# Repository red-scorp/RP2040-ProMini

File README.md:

```
 ______  ______ ______   ______   __     ______     ______           ______  _       _ 
(_____ \(_____ (_____ \ / __   | / /    / __   |   (_____ \         |  ___ \(_)     (_)
 _____) )_____) )____) ) | //| |/ /____| | //| |___ _____) )___ ___ | | _ | |_ ____  _ 
(_____ (|  ____//_____/| |// | |___   _) |// | (___)  ____/ ___) _ \| || || | |  _ \| |
      | | |     _______|  /__| |   | | |  /__| |   | |   | |  | |_| | || || | | | | | |
      |_|_|    (_______)\_____/    |_|  \_____/    |_|   |_|   \___/|_||_||_|_|_| |_|_|
```

# RP2040-ProMini Project

The RP2040-ProMini project aims to create a replacement for the Arduino Pro Mini using the RP2040 MCU.

## RP2040-ProMini Board

The **RP2040-ProMini** board is a 4-layer board designed to accommodate the popular Raspberry Pi RP2040 MCU in the commonly used, but obsolete, Arduino Pro Mini footprint.

Preview:

You can view the [Schematics in PDF format](doc/RP2040-ProMini.pdf) for detailed information.

STEP 3D files are available [with pins](doc/RP2040-ProMini-with-pins.step) and [without pins](doc/RP2040-ProMini-board.step).

Features:

- Arduino Pro Mini compatible pinout
- Partially compatible with Arduino Nano RP2040 Connect pinout
- _(v3.x)_ Detachable USB and JTAG extension board with RESET button
- Dual-core Cortex-M0+ Raspberry Pi RP2040
- Small footprint suitable for DIY projects
- _(v1.x)_ 19 GPIO pins, including 4 analog inputs or _(v2.x-v3.x)_ 21 GPIO pins, including 4 analog inputs
- USB data pins on the side connector
- SWD debugging pins on the side connector
- _(v1.x)_ LDO-based 3.3V power supply with a maximum 16V input or _(v2.x-v3.x)_ Buck-Boost converter based 3.3V power supply with input range of 2.5V-12V
- Supports both SOIC and WSON 16MB flash packages
- Flat back side enables use as a sub-assembly
- Two cut points to reduce power consumption of unused components

CAM files, as well as the BOM and CPL files for JLCPCB, are available.

### Board Pinout

Following pinout is used for the board:

| Board Pin | RP2040 Pin | Function | Notes |
| --------- | ---------- | -------- | ----- |
| D0        | GPIO1      | UART0 TX |       |
| D1        | GPIO0      | UART0 RX |       |
| D2        | GPIO25     |          |       |
| D3        | GPIO15     |          |       |
| D4        | GPIO16     |          |       |
| D5        | GPIO17     |          |       |
| D6        | GPIO18     |          |       |
| D7        | GPIO19     |          |       |
| D8        | GPIO20     |          |       |
| D9        | GPIO21     |          |       |
| D10       | GPIO5      | SS       |       |
| D11       | GPIO7      | MOSI     |       |
| D12       | GPIO4      | MISO     |       |
| D13       | GPIO6      | SCK      | LED   |
| D14 A0    | GPIO26     |          |       |
| D15 A1    | GPIO27     |          |       |
| D16 A2    | GPIO28     |          |       |
| D17 A3    | GPIO29     |          |       |
| D18       | GPIO12     | SDA      |       |
| D19       | GPIO13     | SCL      |       |
| D20       | GPIO22     |          |       |
| D21       | GPIO23     |          |       |

### Cut Points

There are two cut points on the board to reduce power consumption of unused components.

| Cut Point | Function | Notes |
| --------- | -------- | ----- |
| CUT_VIN   | Separates VIN-to-3V3 power supply with power LED from the rest of the board | This cut point is useful if you want to power the board from 3V3 pin instead of VIN pin. |
| CUT_LED   | Separates LED on pin D13 from the rest of the board | This cut point is useful if you want to reduce power consumption of the board. |

## Version History

Roughly RP2040-ProMini board exists in three flavors:

- v1.x - this boards are cheaper because they are based on LDO power supply.
- v2.x - this boards are more expensive because they are based on Buck-Boost power supply.
- v3.x - this boards has same basic design as v2.x but includes detachable USB and JTAG extension board.

The development of v3.x boards is happening in *master* branch, while v1.x and v2.x boards are developed in *dev_v1* and *dev_v2* branches respectively.

Each board version listed below is tagged in its respective branch and includes all the necessary files to manufacture the board.

### v3.2 - 09.02.2024

- Added Gxx pin names on the back of the board.
- Made extension board cut-out openings wider for easier cutting.

### v3.1 - 21.11.2023

- Removed pull-up resistor from SWCLK line.
- Added white silkscreen under LEDs to add light reflection.

### v3.0 - 29.08.2023

- Added detachable USB and JTAG extension board with RESET button.
- Improved routing a bit.

### v2.2 - 01.01.2024

- Added Gxx pin names on the back of the board.

### v2.1 - 21.11.2023

- Removed pull-up resistor from SWCLK line.
- Added white silkscreen under LEDs to add light reflection.

### v2.0 - 23.07.2023

- Use Buck-Boost converter instead of LDO.
- Added two new digital pins.
- Moved few components around.

### v1.3 - 01.01.2024

- Added Gxx pin names on the back of the board.
- Made front and back texts bigger for better readability.

### v1.2 - 21.11.2023

- Removed pull-up resistor from SWCLK line.
- Added white silkscreen under LEDs to add light reflection.

### v1.1 - 05.07.2023

- Moved few components around.
- Added BOOTSEL mini button for programming convenience.
- Changed LED resistors to allow more current, making LED to emit more light.

### v1.0 - 25.06.2023

- Moved few resistors around.
- Added small GND fill under the MCU.
- Switched positions of UD- and GND pins on the side connector.
- Generated different set of BOM and CPL files for SOIC and WSON versions of the board.

### v1.0b1 - 13.06.2023

Initial release for testing purposes.

## Links

- [Raspberry Pi RP2040 information page](https://www.raspberrypi.com/documentation/microcontrollers/rp2040.html).
- [Arduino Pro Mini information page](https://docs.arduino.cc/retired/boards/arduino-pro-mini).
- [Arduino Nano RP2040 Connect page](https://docs.arduino.cc/hardware/nano-rp2040-connect).
- [Arduino SDK for RP2040 board](https://github.com/earlephilhower/arduino-pico).

## How to Help

Your contributions as code, resources, or finances are welcome! Please contact me directly via email at andriy.golovnya@gmail.com or through my [GitHub profile](https://github.com/red-scorp).

If you'd like to make a financial contribution, you can donate via [PayPal](http://paypal.me/redscorp) or [Ko-Fi](http://ko-fi.com/redscorp). Your support is greatly appreciated.

Thanks in advance!

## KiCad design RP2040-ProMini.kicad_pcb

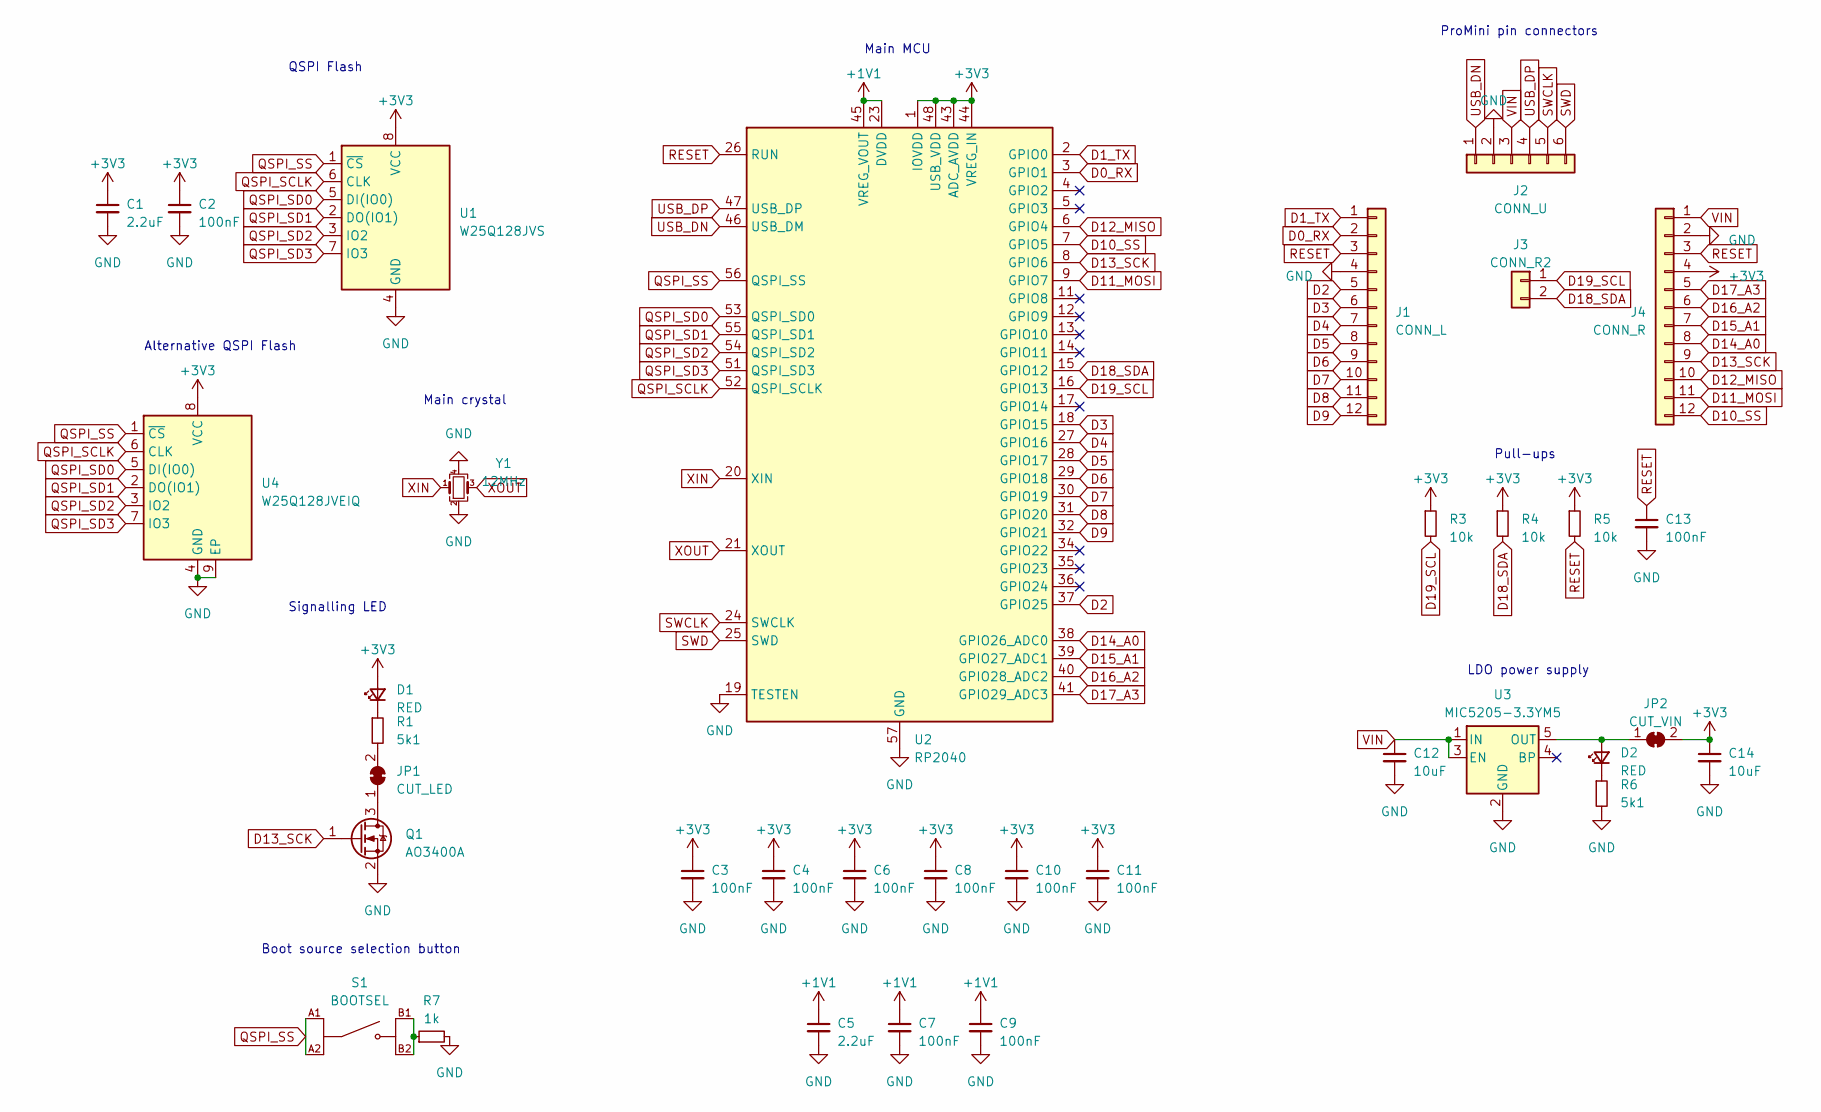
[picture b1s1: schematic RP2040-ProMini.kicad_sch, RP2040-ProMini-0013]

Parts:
C1, C5: 2.2uF; C_0603_1608Metric
C2, C3, C4, C6, C7, C8, C9, C10, C11, C13: 100nF; C_0402_1005Metric
C12, C14: 10uF; C_0805_2012Metric
D1, D2: RED; LED_0603_1608Metric
J1: CONN_L; PinHeader_1x12_P2.54mm_Vertical
J2: CONN_U; PinHeader_1x06_P2.54mm_Vertical
J3: CONN_R2; PinHeader_1x02_P2.54mm_Vertical
J4: CONN_R; PinHeader_1x12_P2.54mm_Vertical
JP1: CUT_LED; SolderJumper-2_P1.3mm_Bridged_RoundedPad1.0x1.5mm
JP2: CUT_VIN; SolderJumper-2_P1.3mm_Bridged_RoundedPad1.0x1.5mm
Q1: AO3400A; SOT-23
R1, R6: 5k1; R_0402_1005Metric
R3, R4, R5: 10k; R_0402_1005Metric
R7: 1k; R_0402_1005Metric
S1: BOOTSEL; SW_EVPBB0AAB000; DIGI-KEY_PART_NUMBER P19888CT-ND
U1: W25Q128JVS; SOIC-8_5.23x5.23mm_P1.27mm
U2: RP2040; QFN-56-1EP_7x7mm_P0.4mm_EP3.2x3.2mm
U3: MIC5205-3.3YM5; SOT-23-5
U4: W25Q128JVEIQ; WSON-8-1EP_6x5mm_P1.27mm_EP3.4x4.3mm
Y1: 12MHz; Crystal_SMD_3225-4Pin_3.2x2.5mm

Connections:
+1V1: C5.1, C7.1, C9.1, U2.23 (DVDD), U2.45 (VREG_VOUT), U2.50 (DVDD)
+3V3: C1.1, C2.1, C3.1, C4.1, C6.1, C8.1, C10.1, C11.1, C14.1, D1.2 (A), J4.4, JP2.2 (B), R3.1, R4.1, R5.1, U1.8 (VCC), U2.1 (IOVDD), U2.10 (IOVDD), U2.22 (IOVDD), U2.33 (IOVDD), U2.42 (IOVDD), U2.43 (ADC_AVDD), U2.44 (VREG_IN), U2.48 (USB_VDD), U2.49 (IOVDD), U4.8 (VCC)
D0_RX: J1.2, U2.3 (GPIO1)
D1_TX: J1.1, U2.2 (GPIO0)
D2: J1.5, U2.37 (GPIO25)
D3: J1.6, U2.18 (GPIO15)
D4: J1.7, U2.27 (GPIO16)
D5: J1.8, U2.28 (GPIO17)
D6: J1.9, U2.29 (GPIO18)
D7: J1.10, U2.30 (GPIO19)
D8: J1.11, U2.31 (GPIO20)
D9: J1.12, U2.32 (GPIO21)
D10_SS: J4.12, U2.7 (GPIO5)
D11_MOSI: J4.11, U2.9 (GPIO7)
D12_MISO: J4.10, U2.6 (GPIO4)
D13_SCK: J4.9, Q1.1 (G), U2.8 (GPIO6)
D14_A0: J4.8, U2.38 (GPIO26_ADC0)
D15_A1: J4.7, U2.39 (GPIO27_ADC1)
D16_A2: J4.6, U2.40 (GPIO28_ADC2)
D17_A3: J4.5, U2.41 (GPIO29_ADC3)
D18_SDA: J3.2, R4.2, U2.15 (GPIO12)
D19_SCL: J3.1, R3.2, U2.16 (GPIO13)
GND: C1.2, C2.2, C3.2, C4.2, C5.2, C6.2, C7.2, C8.2, C9.2, C10.2, C11.2, C12.2, C13.2, C14.2, J1.4, J2.2, J4.2, Q1.2 (S), R6.2, R7.2, U1.4 (GND), U2.19 (TESTEN), U2.57 (GND), U3.2 (GND), U4.4 (GND), U4.9 (EP), Y1.2, Y1.4
unnamed: D1.1 (K), R1.1
unnamed: D2.2 (A), JP2.1 (A), U3.5 (OUT)
unnamed: D2.1 (K), R6.1
unnamed: JP1.1 (A), Q1.3 (D)
unnamed: JP1.2 (B), R1.2
unnamed: R7.1, S1.B1, S1.B2
QSPI_SCLK: U1.6 (CLK), U2.52 (QSPI_SCLK), U4.6 (CLK)
QSPI_SD0: U1.5 (DI(IO0)), U2.53 (QSPI_SD0), U4.5 (DI(IO0))
QSPI_SD1: U1.2 (DO(IO1)), U2.55 (QSPI_SD1), U4.2 (DO(IO1))
QSPI_SD2: U1.3 (IO2), U2.54 (QSPI_SD2), U4.3 (IO2)
QSPI_SD3: U1.7 (IO3), U2.51 (QSPI_SD3), U4.7 (IO3)
QSPI_SS: S1.A1, S1.A2, U1.1 (~CS), U2.56 (QSPI_SS), U4.1 (~CS)
RESET: C13.1, J1.3, J4.3, R5.2, U2.26 (RUN)
SWCLK: J2.5, U2.24 (SWCLK)
SWD: J2.6, U2.25 (SWD)
USB_DN: J2.1, U2.46 (USB_DM)
USB_DP: J2.4, U2.47 (USB_DP)
VIN: C12.1, J2.3, J4.1, U3.1 (IN), U3.3 (EN)
XIN: U2.20 (XIN), Y1.1
XOUT: U2.21 (XOUT), Y1.3

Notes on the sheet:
Alternative QSPI Flash
ProMini pin connectors
Main MCU
Main crystal
Pull-ups
Signalling LED
Boot source selection button
LDO power supply
QSPI Flash

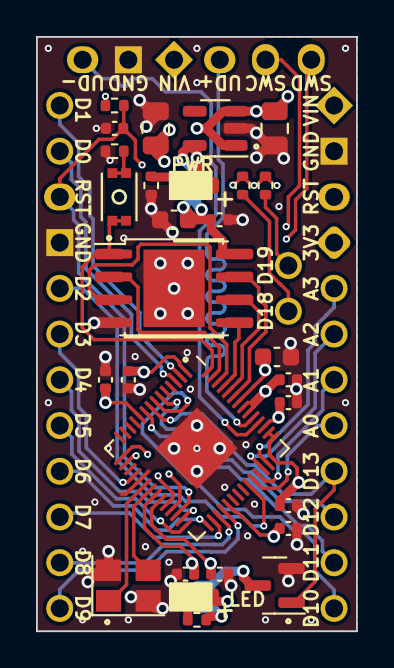
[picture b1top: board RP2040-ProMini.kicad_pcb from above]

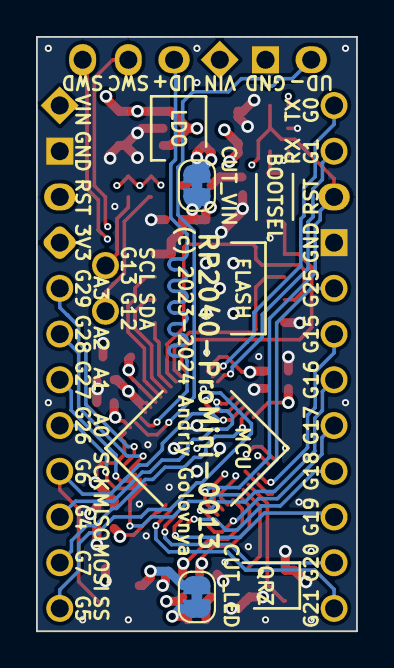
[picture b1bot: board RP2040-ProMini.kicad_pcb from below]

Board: 4 copper layers, 17.8 x 33.0 mm, 35 parts (6 on the bottom side), 43 nets.

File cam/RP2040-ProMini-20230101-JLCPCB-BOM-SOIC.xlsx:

Qty | Designator | Footprint | JLCPCB Part# | Comment
2 | C14,C12 | 0805 | C15850 | 10uF
2 | D2,D1 | 0603 | C2286 | RED
10 | C10,C6,C7,C9,C13,C4,C2,C11,C3,C8 | 0402 | C1525 | 100nF
2 | C1,C5 | 0603 | C1604 | 2.2uF
3 | R4,R3,R5 | 0402 | C25744 | 10k
1 | U1 | SOIC-8-208mil | C97521 | W25Q128JVS
1 | Y1 | SMD3225-4P | C9002 | 12MHz
1 | U2 | LQFN-56(7x7) | C2040 | RP2040
1 | Q1 | SOT-23-3L | C20917 | AO3400A
1 | U3 | SOT-23-5 | C37970 | MIC5205-3.3YM5
1 | S1 | SMD,1.6x2.6mm | C913786 | 1TS026A-1800-0553-CT
1 | R7 | 0402 | C11702 | 1k
2 | R1,R6 | 0402 | C25905 | 5k1

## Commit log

2023-05-31 Initial schematics
2023-06-01 Added basic power input
2023-06-01 Added whole bunch of things
2023-06-02 Removed 2-pin connector. Routed power traces and fills. Started to route traces.
2023-06-03 Routed few more traces
2023-06-04 Finished routing of the board.
2023-06-05 Optimized routing a bit
2023-06-06 Optimized routing a lot.
2023-06-07 Optimized routing even more.
2023-06-08 Shaped solder areas for non-gpio pins. Added back silkscreen drawings.
2023-06-09 Optimized few traces on PCB. Added few descriptive texts on schematics.
2023-06-09 Generated CAM files
2023-06-09 Generated BOM and CPL files
2023-06-09 Generated BOM file
2023-06-09 Generated PDF schematics
2023-06-09 Updated project file
2023-06-09 Added PNG previews
2023-06-09 Renamed images
2023-06-09 Added README.md
2023-06-10 Fixed USB trace
2023-06-10 Improved README.md
2023-06-11 Added round tracks config file
2023-06-11 Reduced minimum width of fills.
2023-06-11 Added alternative footprint for flash chip
2023-06-11 Moved few stuff around.
2023-06-12 Moved some traces around
2023-06-13 Generated PNG previews
2023-06-13 Updated release date
2023-06-17 Moved few resistors for proper alignment
2023-06-17 Generated CAM files for SOIC and WSON version of flash chip
2023-06-22 Switched D- and GND on debug connector. Added missing VIN text.
2023-06-24 Changed pads shape after flipping UD- and GND around
2023-06-24 Generated CAM files.
2023-06-24 Added GND plane under the MCU. Generated CAM files.
2023-06-24 Updated README.md with prospected v1.0 history
2023-07-04 Added BOOTSEL button for user convenience
2023-07-04 Moved few stuff around for better routing
2023-07-05 Added 3D model for BOOTSEL mini button.
2023-07-05 Spin off v1.1 to reflect new BOOTSEL button.
2023-07-05 Moved Q1 to the side a bit.
2023-07-05 Generated CAM, BOM and CPL files
2023-07-05 Ren DRC check
2023-07-09 Added buck-boost converter TPS63060 instead of LDO
2023-07-09 Added D20 and D21. Fixed minor issues. Moved stuff around.
2023-07-10 Moved few traces around.
2023-07-10 Moved KiCad libraries and 3D file to lib folder
2023-07-12 Moved few traces and vias around.
2023-07-12 Made silkscreen texts bigger for better readability
2023-07-12 Removed drawings on the back side
2023-07-12 Added FUNDING.yml
2023-07-13 Moved few traces and texts around.
2023-07-13 Changed pin number texts, removed D letter
2023-07-13 Rotated quartz for better silk markings alignment
2023-07-13 Adjusted few texts
2023-07-13 Moved few stuff around
2023-07-16 Moved few stuff around. Added storage cap.
2023-07-16 Moved second row of texts a bit.
2023-07-16 Moved few vias around for better soldering
2023-07-16 Moved few stuff around. Added designed in Germany test.
2023-07-16 Added few descriptive texts on schematics
2023-07-16 Checked DRC
2023-07-17 Aligned schematics components to bigger grid
2023-07-17 Generated STEP 3D model
2023-07-20 Updated README.md for v2.0.
2023-07-23 Removed pins from exports.
2023-07-23 Added second STEP 3D file without pins.
2023-07-23 Added previous version preview images.
2023-08-05 Added removable USB and debug extension board.
2023-08-05 Upgraded kicad.
2023-08-05 Updated README.md with v3.0 board information and ASCII batter
2023-08-05 Updated banner text
2023-08-05 Updated DRC rules check
2023-08-06 Updated release date.
2023-08-07 Modified VOUT traces
2023-08-09 Updated README.md with v3.0 board information
2023-08-28 Added link to compatible Arduino SDK. Fixed a typo.
2023-08-29 Improved README.md for better visuals.
2023-09-01 Moved a power trace a bit.
2023-11-11 Moved stuff around.
2023-11-11 Added white color under the LEDs to add light reflection.
2023-11-21 Removed pull-up resistor for SWDCLK line.
2023-11-21 Increased board version
2023-11-21 Generated PDF schematic
2023-11-21 Resolved DRC issues
2023-11-21 Changed JTAG connector
2023-11-22 Made but off gap wider for easier production and use.
2023-12-04 Fixed typo
2023-12-14 Added rough versions division explanation
2023-12-14 Fixed README a bit
2023-12-29 Added board pinout information
2023-12-30 Renamed Arduino pins as Dxx. Added GPIO pin names at the back as Gxx.
2024-01-01 Changed board version to 3.2.
2024-01-01 Updated copyright year values.
2024-01-01 Changed board version to 2.2.
2024-01-01 Generated PNG preview
2024-01-01 Brought description from v2 branch
2024-01-01 Changed board version to 1.3.
2024-01-01 Added GPIO pin names at the back as Gxx.
2024-01-01 Made front and back texts bigger for better readability
2024-01-01 Updated README.md with information about v1.3
2024-01-02 Added version release dates to README
2024-01-02 Added development branches description into README.md
2024-01-02 Added tags information to README.md
2024-02-09 Update v3.2 date.

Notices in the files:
RP2040-ProMini.kicad_pcb:
(c) 2023-2024 Andriy Golovnya
